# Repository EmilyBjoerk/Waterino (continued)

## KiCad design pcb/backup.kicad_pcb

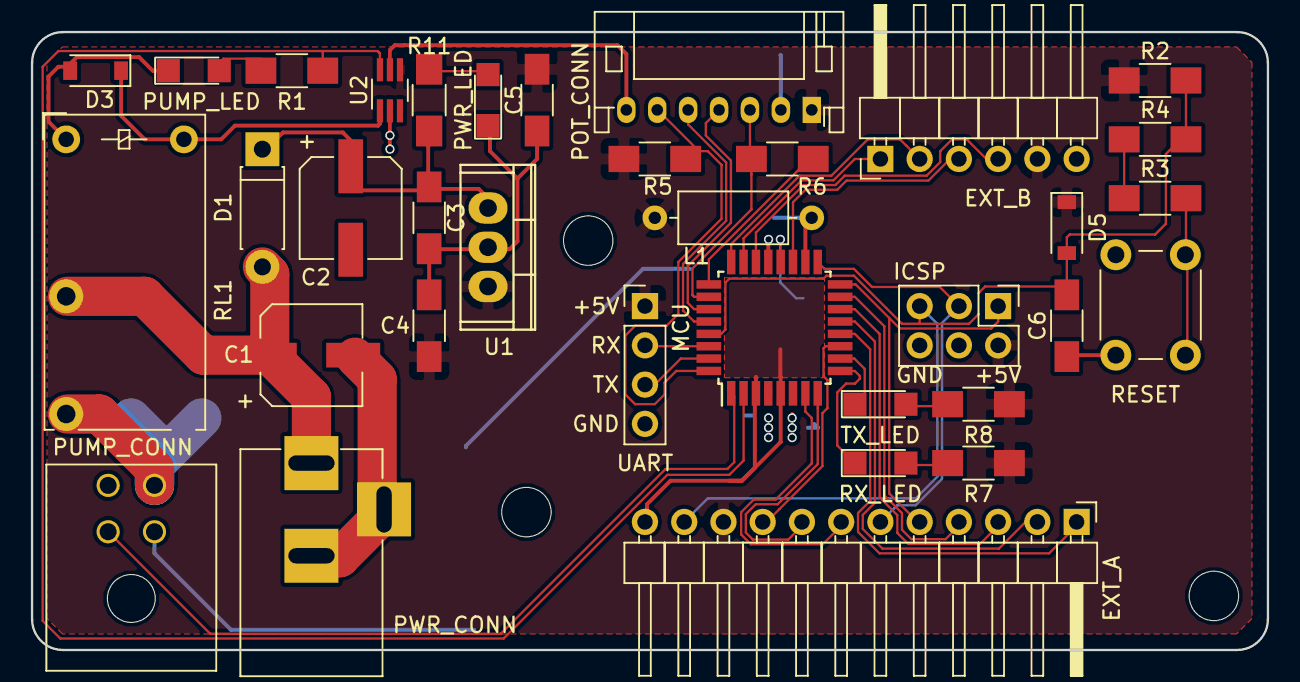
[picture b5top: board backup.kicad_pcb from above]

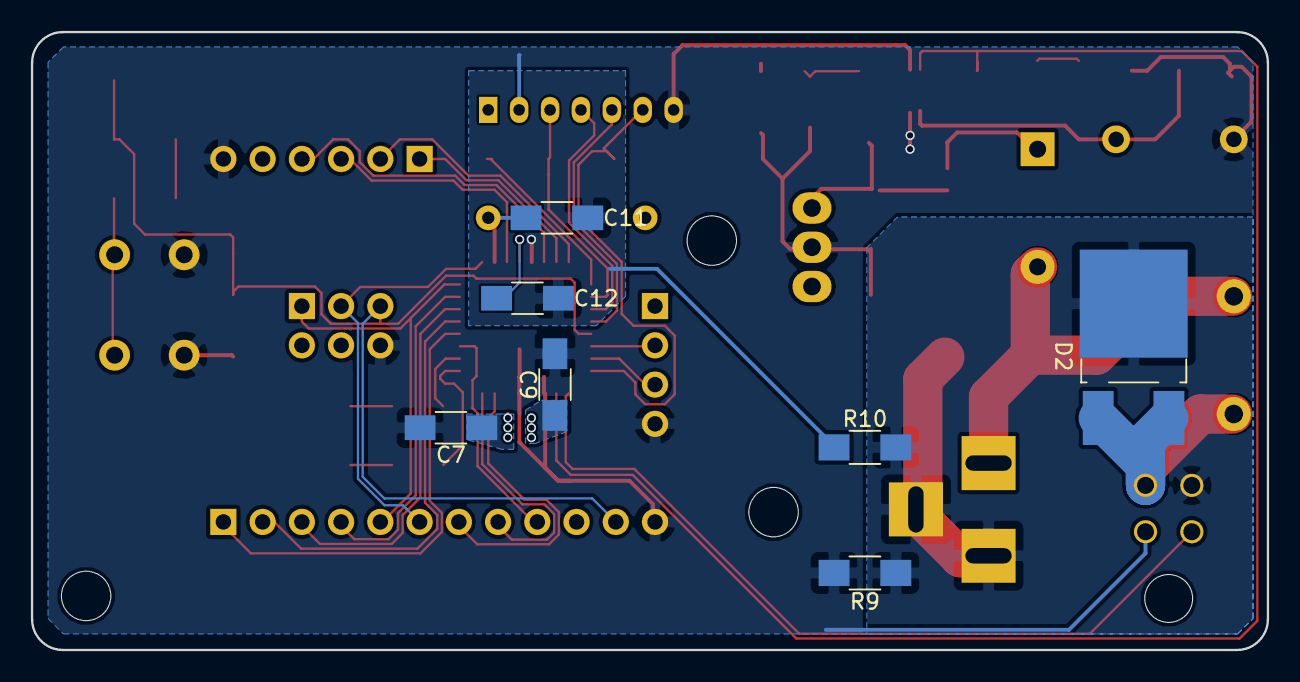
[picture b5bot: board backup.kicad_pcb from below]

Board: 2 copper layers, 80.0 x 40.0 mm, 42 parts (7 on the bottom side), 41 nets.

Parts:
C1, C2: 100µF; CP_Elec_6.3x7.7
C3, C4, C5, C6, C7, C9, C11: 100nF; C_1206_HandSoldering
C12: 10nF; C_1206_HandSoldering
D1: D; D_DO-41_SOD81_P7.62mm_Horizontal
D2: D_Schottky; TO-252-2_Rectifier
D3, D5: D_Schottky; D_SOD-123
EXT_A: CONN_01X12; Pin_Header_Angled_1x12_Pitch2.54mm
EXT_B: CONN_01X06; Pin_Header_Angled_1x06_Pitch2.54mm
ICSP: CONN_02X03; Pin_Header_Straight_2x03_Pitch2.54mm
L1: 10µH; L_Axial_L7.0mm_D3.3mm_P10.16mm_Horizontal_Fastron_MICC
MCU: ATMEGA168-20AU; TQFP-32_7x7mm_Pitch0.8mm
POT_CONN: CONN_01X07; JST_PH_S7B-PH-K_07x2.00mm_Angled
PUMP_CONN: CONN_02X02; Molex_Microfit3_Header_02x02_Angled_43045-040x
PUMP_LED: PUMP_LED; LED_1206
PWR_CONN: BARREL_JACK
PWR_LED: PWR_LED; LED_1206
R1: 1.5k; R_1206_HandSoldering
R2: 4k7; R_1206_HandSoldering
R3, R4: 150; R_1206_HandSoldering
R5: 100k; R_1206_HandSoldering
R6: 10k; R_1206_HandSoldering
R7, R8: 150R; R_1206_HandSoldering
R9, R10: 0; R_1206_HandSoldering
R11: 1.5K; R_1206_HandSoldering
RESET: SW_PUSH; SW_PUSH_6mm
RL1: FINDER-32.21-x300; Relay_SPST_Finder_32.21-x300
RX_LED: RX_LED; LED_1206
TX_LED: TX_LED; LED_1206
U1: LM7805CT; TO-220
U2: MIC94090; SOT-363_SC-70-6_Handsoldering
UART: CONN_01X04; Pin_Header_Straight_1x04_Pitch2.54mm

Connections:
+12V: C1.1, D1.2, PWR_CONN.1, RL1.11
/COIL_PWR: D3.1, RL1.A2, U2.1
/PUMP+: D2.1, PUMP_CONN.3, RL1.14
AVcc: C11.1, L1.2, MCU.18
AVss: C11.2, C12.2, MCU.21, R10.1
EXT_A0: EXT_B.1, MCU.23
EXT_A1: EXT_B.2, MCU.24
EXT_A2: EXT_B.3, MCU.19
EXT_A3: EXT_B.4, MCU.22
EXT_D0: EXT_A.1, MCU.12
EXT_D1: EXT_A.2, MCU.13
EXT_D2: EXT_A.3, MCU.14
EXT_D3: EXT_A.7, MCU.7
EXT_D4: EXT_A.8, MCU.8
EXT_D5: EXT_A.9, MCU.11
GND: C2.2, C3.2, C4.2, C5.2, C6.2, C7.2, C9.2, D3.2, EXT_A.12, EXT_B.6, ICSP.6, MCU.3, MCU.5, POT_CONN.2, POT_CONN.7, PUMP_CONN.1, PUMP_LED.1, PWR_LED.1, R9.2, RESET.1, RL1.A1, U1.2, U2.2, U2.5, UART.4
MISO: EXT_A.5, ICSP.1, MCU.16
MOIST+: MCU.25, R6.2
MOIST-: MCU.27, POT_CONN.4
MOISTURE: MCU.26, POT_CONN.3, R6.1
MOSI: EXT_A.4, ICSP.4, MCU.15
unnamed: C12.1, MCU.20
unnamed: PUMP_LED.2, R1.1
unnamed: R7.2, RX_LED.2
unnamed: R8.2, TX_LED.2
unnamed: PWR_LED.2, R11.2
unnamed: R3.1, RESET.2
unnamed: R3.2, R4.1
PGND: C1.2, D2.2, PUMP_CONN.4, PWR_CONN.2, PWR_CONN.3, R9.1, R10.2
PUMP: MCU.2, R1.2, U2.6
REG_PWR: C2.1, C3.1, D1.1, R11.1, U1.1
RX: MCU.30, UART.2
RX_LED: MCU.9, RX_LED.1
SCK: EXT_A.6, ICSP.3, MCU.17
THERM: MCU.28, POT_CONN.5
TX: MCU.31, UART.3
TX_LED: MCU.10, TX_LED.1
Vcc: C4.1, C5.1, C7.1, C9.1, D5.1, EXT_A.10, EXT_B.5, ICSP.2, L1.1, MCU.4, MCU.6, POT_CONN.1, R2.2, R5.1, R7.1, R8.1, U1.3, U2.4, UART.1
~LEVEL_ALERT: MCU.1, PUMP_CONN.2
~OVRFLW: MCU.32, POT_CONN.6, R5.2
~RESET: C6.1, D5.2, EXT_A.11, ICSP.5, MCU.29, R2.1, R4.2

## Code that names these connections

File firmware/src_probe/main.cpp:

#include <avr/interrupt.h>
#include <avr/sleep.h>

#include "xtd_uc/adc.hpp"
#include "xtd_uc/eeprom.hpp"
#include "xtd_uc/i2c.hpp"

#include "probe.hpp"
#include "proto_fsm.hpp"

// SDA/SCA = PB0/PB2
// MOIST_P_PIN = PB5
// MOIST_N_PIN = PB1
// MOIST_A_PIN = PB3/ADC3
// TEMP_A_PIN = PB4/ADC2

xtd::i2c_device i2c;
xtd::eeprom_small<uint8_t, 0> i2c_addr;
probe::protocol_fsm protocol;

ISR(ADC_vect) {  // else application is reset
}

ISR(TWI_vect) {
  auto state = i2c.on_twi();
  switch (state) {
    case xtd::i2c_slave_transmit:
      break;
    case xtd::i2c_slave_receive:
      break;
    case xtd::i2c_master_lost_arbitration:
      break;
    case xtd::i2c_master_nobody_home:
      break;
    case xtd::i2c_master_transmit:
      break;
    case xtd::i2c_master_receive:
      break;
    case xtd::i2c_master_idle:
      break;

    case xtd::i2c_idle:            // FALLTHROUGH
    case xtd::i2c_busy:            // FALLTHROUGH
    case xtd::i2c_internal_error:  // FALLTHROUGH
    default:
      // Do nothing
  }
}

int main() {
  // Make sure probe excitation pins are in the default state
  probe::stop_excitation();

  // Disable power to timers (not used) other flags handled below
  PRR = _BV(PRTIM1) | _BV(PRTIM0);

  // Disable digital input on the probe excitation pins (never read)
  DIDR0 |= _BV(ADC0D);  // MOIST+ (PB5/RESET)
  DIDR0 |= _BV(AIN1D);  // MOIST- (PB1)

  // Disable Analog comparator circuitry
  xtd::set_bit(ACSR, ACD);

  // Disable digital io on PB3/4 (used as ADC) to save power
  xtd::adc_dio_pin(2, false);
  xtd::adc_dio_pin(3, false);
  xtd::adc_disable();

  // Setup i2c slave driver
  i2c.enable(0);
  i2c.slave_on(15 << 1, false);

  // Setup is done enable interrupts
  sei();

  while (true) {
    protocol.run(i2c);

    // Mask interrupts so that the i2c driver doesn't become active immediately after reporting idle
    cli();
    if (protocol.can_sleep()) {
      set_sleep_mode(i2c.idle() ? SLEEP_MODE_PWR_DOWN : SLEEP_MODE_IDLE);
      sleep_enable();

      // Next instcuction will execute before interrupts are processed meaning that any...
      sei();
      // ...pending IRQ since cli() above will wake the cpu and return from the sleep call
      sleep_cpu();
      sleep_disable();
    } else {
      sei();
    }
  }
}

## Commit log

2017-05-07 Initial commit.
    Still a work in progress.
2017-05-14 Ready to start dry run.
2017-06-04 Work in progress.
2017-06-19 Finally got it all together and ordered
2017-07-08 Cleaning up code and fixing compile errors.
2017-07-08 Cleaning up PCB files.
2017-07-08 Adding libraries and cleaning up some more.
2017-07-18 Fixing compile issues and adding a self-test program to test soldering connections on a new waterino.
2017-07-20 Adding a callback for doing some quick processing after IRQs in sleep.
2017-07-22 Perform the irq_wake only if there is enough time left
2017-07-22 Making sleep actually do what it says on the tin.
2017-07-22 Reworking bits to fit together.
2017-07-22 Adding RX led to the command interpreter.
2017-07-22 Hopefully everything is in place now.
2017-07-22 Removing cruft.
2018-05-12 Update README.md
    Saving changes in between.
2018-05-12 Adding logo and making thing compile again.
2018-05-12 Fixing wrong part nr in BOM.
2018-05-12 Fixes #10.
2018-05-12 Missed one file in #10.
2018-05-12 wip on #9
2018-05-12 Restructuring makefile to accomodate native unit tests in preparation for #19.
2018-05-13 Fixes #9.
2018-05-13 Adding simulation script for octave/(matlab) of the controller.
2018-05-14 Adding unit tests to the controller.
2018-05-25 Adding schematic for the probe.
2018-05-25 Adding more tests and starting to clean up and hopefully be able to test more parts.
2018-05-25 More WIP on #19.
2018-05-25 Updating gitignore for new coverage files and binaries.
2018-05-25 Adding script to easily show coverage information of tests.
2018-05-27 Adding brandbook.
2018-05-27 Cleaning up hardware files.
2018-06-15 Probe B as Rev 1 as manufactured.
2018-07-12 Fixes #21. Also removes RC filters that made the output impedence too high for the ADC. Changed connector to Micro USB due to cable availabiliy. Changed to a more reasonable inline ferrite and also r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
2018-07-29 Fixing makefile and adding first code fragments for the probe
2018-07-30 Managed to flash blinky on the attiny with arduino as isp.
2018-07-31 Soon ready for first test of i2c on attiny
2018-08-05 Protocol seems to be ready for testing/data collection.
2018-08-06 Can now get raw data from probe
2018-08-08 Cleaning up a bit
2018-08-09 A smaller implementation of the protocol
2018-10-07 Trying to refactor fi rmware to fit new hardware design
2018-10-20 WIP rewriting firmware to match new system design.
2018-10-20 Upgrading project to kicad 5.0 and fixing some issues with the last revision.
2018-10-20 Add the source files for the artwork.
2018-12-09 Mostly migrated to CMake, uploading not tested yet. Also code now compiles, some methods are stubs.
2018-12-09 Bumping xtd_uc version.
2019-03-17 WIP on testing.
2019-03-24 The pump and unit tests code is now WAI and tested.
2019-04-09 Fixing submodule after the history wipe.
2019-04-15 Cleaning up old files and getting tests in order.
2019-04-15 Bumping xtd version.
2019-04-21 Both unit tests and avr targets compile. Added status build targets. Ready for test on hardware next.
2019-04-21 Tweaking the coverage script.
2019-04-28 WIP, getting calibration done now and fixing issues.
2019-04-28 Bumping xtd_uc after bugfixes in the library.
2019-04-28 Fixing corrupted output
2019-04-28 Remove old unused code attempts.
2019-04-28 Cleaning up code.
2019-04-28 More cleaning up.
2019-05-01 Tidying up the art folder.
2019-05-01 Adding rendered version of arch diagram.
2019-06-08 V3 of the node.G
2019-06-15 Updating layout of node and art.
2019-06-24 Performing experiment with emulating 555 timer on the ATmega. Seems to work.
2019-06-25 Rewriting parts of the application to fit with new hardware.
2019-07-05 Unit tests compile again, but don't pass. #snapshot.
2019-07-09 Fixing tests and fixing other issuse with the new code for the new hardware revision.
2019-07-10 Minor tweaks to hardware.
2019-07-19 Fixes several bugs from the initial draft version. Including wrong constant conversion of rc_capacitance, too low max rc_capacitance value, change the rc_counts to not overflow so badly, fix timing i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
2019-07-20 Enabling WDT, Fixing inversion of NTC voltage and fixing overflow detection code.
2019-07-20 Change back the programmer and frequency parameters changed while testing last commit.
2020-03-02 Clean up some older files and refactor a bit to make it easier to follow.
2020-03-02 Remove the usage of the old gpio library.
2020-03-02 Fix problem in hal::fatal.
2020-03-13 More refactoring, fixing bugs and broken unit tests.
2020-07-05 snapshot of wip
